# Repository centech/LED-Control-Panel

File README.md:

# LED-Control-Panel
How i created a backlit RGB-LED Control Panel for my kids (Report / DIY Guide)

- [Overview](#overview)
    + [List of used components](#list-of-used-components)
    + [Inspiration](#inspiration)
- [Report](#report)
    + [The Electronics](#the-electronics)
    + [The Panel](#the-panel)
    + [Cable Assembly](#cable-assembly)
    + [Soldering the Connector-Board](#soldering-the-connector-board)
    + [Building the wood casing](#building-the-wood-casing)
    + [Done](#done)

## Overview

Final results first of cause :)

What follows is a list of my used components, as well as a few words where i took my inspiration. Finally the detailed report with a few suggestions for potential recreations. 
But make sure to read through, since i made some glorious errors :)

### List of used components

- [LED RGB Stipes 5050 5M IP20](https://www.aliexpress.com/item/SMD-5050-3014-3528-5630-LED-Strip-RGB-Led-String-Light-Fita-de-Led-Ribbon-Bombillas/32554704554.html) (4,26 Euro per 5 meters)
- [LED Switch 3x](https://www.aliexpress.com/item/16mm-red-blue-yellow-green-white-Light-Hot-Car-Auto-Metal-LED-Power-Push-Button-Switch/32800304223.html) (1,27 Euro each)
- [LED Rocker Switch 1x](https://www.aliexpress.com/item/4pcs-lot-4models-Car-DIY-23mm-Mini-Round-Rocker-Switch-12V-16A-LED-illuminated-toggle/32801141576.html) (1,31 Euro each)
- [PWM Controler 3x](https://www.aliexpress.com/item/PWM-DC-6V-12V-24V-28V-3A-Max-Motor-Speed-Control-Module-DC-Motor-Switch-Controller/32667220339.html) (1 Euro each)
- [Cables](https://www.aliexpress.com/item/Tinned-copper-22AWG-led-RGB-cable-4-pin-RGB-cable-PVC-insulated-wire-22-awg-UL2468/32816156735.html)(0,47 Euro per meter)
- [Power Supply](https://www.amazon.de/gp/product/B01N9MSILM/ref=oh_aui_detailpage_o01_s00?ie=UTF8&psc=1) (8,99 Euro each)
- [Thread inserts 20x](https://www.ebay.de/itm/332450417100) (2,86 Euro for 20 pieces)
- [Green LED for backlighting](http://de.farnell.com/optek-technology/ovllg8c7/led-5mm-green/dp/1678694) (0.34 Euro each)
- Wood of your choice and disposal (4 Euro)

- Total material costs approx: **35 Euro**

The most expensive piece was the custom panel i made with [Ponoko](https://www.ponoko.com/) but this was mainly because of the high shipping costs to Germany.
I've used the [Black on White](https://www.ponoko.com/make-and-sell/show-material/607-acrylic-two-color-black-on-white) material. Depending on your design and shipment location you might be able to 
create this panel much cheaper.

**Panel costs:**
- Making $30.03
- Materials $12.00  
- Shiping $34.77 

Total costs approx: **96 Euro ($120)**

### Inspiration

Since i saw the [Spaceship Panel](https://imgur.com/gallery/dqK7A) Cody2084 created i wanted to make something similar for my kids. I loved the idea of creating
something - anything - which was backlit and had buttons on it :). So when i needed a bit more light in the room of my kids this was the perfect excuse to create
a **RGB-LED Control Panel**! It has to be backlit of cause (how could you see it otherwise? Its dark in the room, remeber?). And of cause it needed to have big colorful buttons.
How else would the kids be able to use it? And its not like you could simply buy these control modules, right? So in this dire situation i was practically without any other option: **i had to build it on my own**!

Before i dive into my report, i want to thank Cody2084 again for his great report on his Spaceship Panel, i hope he doesn't mind that i took quite some inspirations from it.

## Report

Ok before you start make sure that you choose the right buttons, switches and controls for your panel. The diversity is huge.

I wanted the following features/requirements fullfilled by my control panel

- LED color and brightness should be fully adjustable
- There should be a fast way to get the LED to full brightness and white color. But this feature should not wipe the settings of the custom adjusted color and brightness.
- The module shoult have an on/off switch
- All controls should have a connector, so that the panel would be easy to remove
- Of cause the module should be backlit
- I didn't want to solder the ICs on my own while i was fine with soldering a few wire lines and connectors

### The Electronics

I'm sure there are better solutions out there but i found these PWM modules to control the RGB LEDs. Its actual purpose is to control motors. But i found out that it worked just fine as a RGB controler.
So thats how it would be able to adjust each color individually. 

Now to be able to "overwrite" this settings i decided to use three switches (red, green, blue) to get each LED in full brightness mode with a simple press. 

By combining these buttons one could create a total of 7 colors (red, green, blue, cyan, magenta, yellow, white).

This is the [board schematic](/board/board.sch) i came up with. Feel free to use and optimize it. Please bear in mind that at that point i didn't think about writing a report about my project. Thats why its looking very crude.

Here is the [board layout](/board/board.brd). Red lines are cables, blue lines are soldered wires on the board. (I leave this here for completeness but do your self a favour and create your own, better schematic and layout!).

### The Panel

Beeing sure on what components to use i started designing the panel. As mentioned before I've used the [Black on White](https://www.ponoko.com/make-and-sell/show-material/607-acrylic-two-color-black-on-white) material from Ponoko. I wasn't sure if the white is translucent enough for the backlighting but since there was no other fitting material available i took the risk.
Ponoko has some easy to understand tutorials and templates. So it was easy enough to create my design. I've [uploaded it here](/panel/Panel.svg), feel free to use it as a template. 

In retrospective i would probably increase the drilling holes for the PWMs and switches to allow for a little more tolerance. Otherwise it turned out to be just perfect! Make sure to leave a big enough border, since there will be the wood frame and no backlight can reach this region. Also add a cutting line on the perimeter for a clean material cut and also include the mounting holes. By the way i used the free software [Inkscape](https://inkscape.org/) and it worked like a charm.

### Cable Assembly

As mentioned above i wanted the switches to have a connector, so the panel would be easily demountable. So its soldering time! 

Make sure you mark every signal with a specific color. And don't let your concentration slip in the process. As you might be able to tell, i got the coloring wrong on one switch and had to mark these otherwise.

The cable for the PWM needs to be open ended. Make sure to coat the ends slightly with a bit of solder.

I decided to solder the cable for the LED-Strap directly to the strap. Make sure that the cable is long enough. Do not worry if its to long, you can put the rest of it into the box later.

At last i prepared the LEDs for the backlight.

**Lessons learned**

Although i was pretty happy with the cable assembly at this time, it was not very well thought out in retrospective. In a rebuild i would certainly change the following: 

1. Make the cables **much longer**! I can't stress this enough: at least trippling the cables lenght would have saved me a lot of hassle. It seems counter intuitive at first but you can achive a much more cleard and sorted cable harness in the box if the cables are long enough. With such short cables the box seems much more crowded and its cumbersome to lift the panel and detach the connectors. Also its bad for the backlight if the cables are not sorted properly.

2. If you think you are smart by soldering connectors to your switches make at least sure that every switch gets its own connector. If not, well we will see that later.

### Soldering the Connector-Board

Since i forgot to add the power supply for the LEDs in the switches to the schematic i've added a 10 Pin Socket with 12V/GND outputs to the board afterwards.

I've also added a 12 Pin Socket (in series connected) to hook up 4 LEDs for the backlight. The suggested supply voltage for the LEDs is 3.4V. Using my 12-Pin Socket and powering it with the 12V supply i get an effective supply voltage of 3V at every LED, which works just fine. This way i didn't need to  convert the supply voltage or to use series resistors.

After thats done. Throw some voltages and ampers at it and look if it is working!

Hooray it does! I played several minutes with it, but lets get back to work.

### Panel Assembly

So now lets simply insert all the switches to the panel and thats it. Hey why do we need a chapter for this simple task anyway?

Ok here is the task: grab the below 3 switches (which are conveniently connected to 2 intertwined connectors) and click these into the 3 holes of the panel.

Sure, you would have known better than me, thats not going to work :(

So unwrap the heat shrink and disassemble the pins:

Now thread it through the holes of the panel and assemble it again.

Hooray its still working:

Feel free to skip this chapter entirely by beeing smarter than me in the first place :)

### Building the wood casing

First measure out your frame. In my case the area of the panel was 18x18cm, so i decided to make each piece of the frame 18.5x8cm. I though making the frame slightly bigger then the panel wouldn look as crude as making it smaller and it allows for some tolerances. Make sure to cut it on the right side of the line, because your blade will make the length of the pieces smaller otherwise. When measuring i add the width of the blade to the next length of the piece to compensate for that effect.

Now mark the edges of each piece. I decided to give them all a simple 45° cut and it turned out pretty good.

After the frame is done, measure out the buttom, saw it, and put everything together. If something does not fit right, you may now correct it.

In my case everything was to my satisfaction and i continue with marking all drills for the threads and cable exits.

The downside of the PWM boards is that the knob is directly soldered to the board, this way i needed the board to be on the very edge of the frame.

At that point i realized i didn't had a fitting drill for my router. So i decided to use an even more advanced tool: the **battery-powered screwdriver**!

Screwing in the threads is not so easy. I also drilled 2 holes in the backpanel to make it easiert to mount it to the wall.

Now glue the frame togher. After that glue the frame to the buttom.

In the meantime i applied a natural [oil/wax mixture](https://www.amazon.de/gp/product/B002AP6YBW/) for protection and better look.

After thats done i assembled the PWMs to the frame:

As it turns out the knobs don't stand out enough of the panel. My quick work-around was to glue a little piece of wood under the spacers. This did the trick.

To optimize the backlight i coated the inside of the box with aluminum foil.

To get an impression of the effect i made two test photos:

It may does not immediately stand out but by looking at the illumination of the flashlight, especially the silver body of it one can clearly see much improvement.

After the box was nearly finished i applied the panel to the box, marked the holes for the mouting and put it the threads.

Since everything worked out, i finally glued it the power supply socket and mounted the 4 backlight LEDs to the frame:

### Done

Finally done! I'm very pleased how it turned out. The backlight effect is better than i hoped for. As always there are quite a few things i would have done different in retrospective, above all allowing for much longer cables to be able to mount the cables to the frame. This wasn't possible this time and effects the handling and backlight. But all in all it was a very fun project and i am very happy how it turned out.

Mounting it to the wall and let the kids play.
Ofcause I need to regularly test it to insure its still working properly :)

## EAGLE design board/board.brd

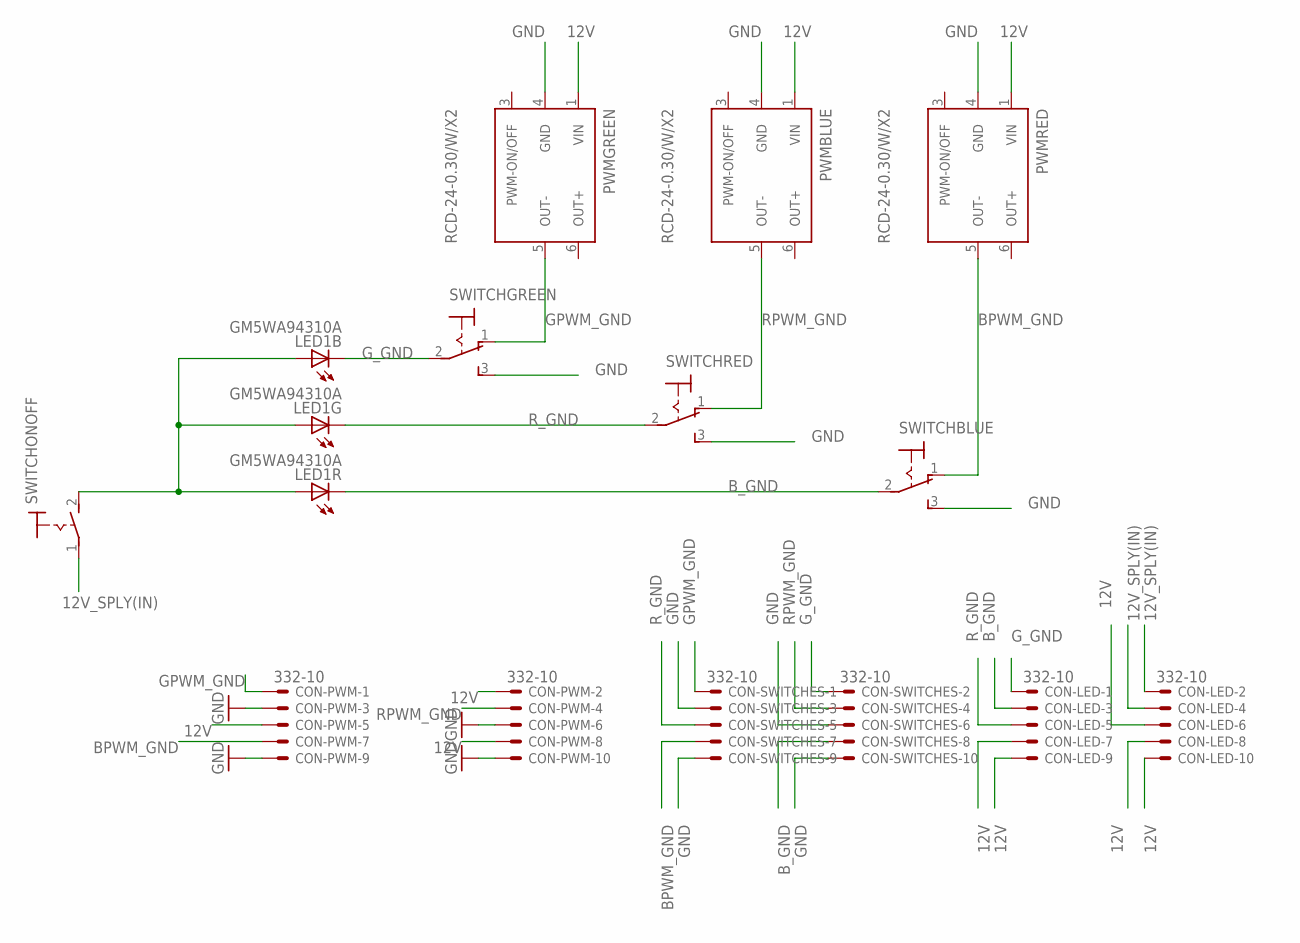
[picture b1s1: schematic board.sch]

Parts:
CON-LED: 332-10
CON-PWM: 332-10
CON-SWITCHES: 332-10
LED1: GM5WA94310A
PWMBLUE: RCD-24-0.30/W/X2; RCD-24/W/X2
PWMGREEN: RCD-24-0.30/W/X2; RCD-24/W/X2
PWMRED: RCD-24-0.30/W/X2; RCD-24/W/X2
SWITCHBLUE: M9040P
SWITCHGREEN: M9040P
SWITCHONOFF: MS243
SWITCHRED: M9040P

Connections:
12V: CON-LED.6, CON-LED.7, CON-LED.8, CON-LED.9, CON-LED.10, CON-PWM.2, CON-PWM.5, CON-PWM.8, LED1.1 (A), LED1.2 (A), LED1.3 (A), PWMBLUE.1 (VIN), PWMGREEN.1 (VIN), PWMRED.1 (VIN), SWITCHONOFF.2 (S)
12V_SPLY(IN): CON-LED.2, CON-LED.4, SWITCHONOFF.1
BPWM_GND: CON-PWM.7, CON-SWITCHES.7, PWMRED.5 (OUT-), SWITCHBLUE.1 (O)
B_GND: CON-LED.3, CON-SWITCHES.8, LED1.5 (C), SWITCHBLUE.2
GND: CON-PWM.3, CON-PWM.6, CON-PWM.9, CON-PWM.10, CON-SWITCHES.3, CON-SWITCHES.6, CON-SWITCHES.9, CON-SWITCHES.10, PWMBLUE.4 (GND), PWMGREEN.4 (GND), PWMRED.4 (GND), SWITCHBLUE.3 (S), SWITCHGREEN.3 (S), SWITCHRED.3 (S)
GPWM_GND: CON-PWM.1, CON-SWITCHES.1, PWMGREEN.5 (OUT-), SWITCHGREEN.1 (O)
G_GND: CON-LED.1, CON-SWITCHES.2, LED1.6 (C), SWITCHGREEN.2
RPWM_GND: CON-PWM.4, CON-SWITCHES.4, PWMBLUE.5 (OUT-), SWITCHRED.1 (O)
R_GND: CON-LED.5, CON-SWITCHES.5, LED1.4 (C), SWITCHRED.2

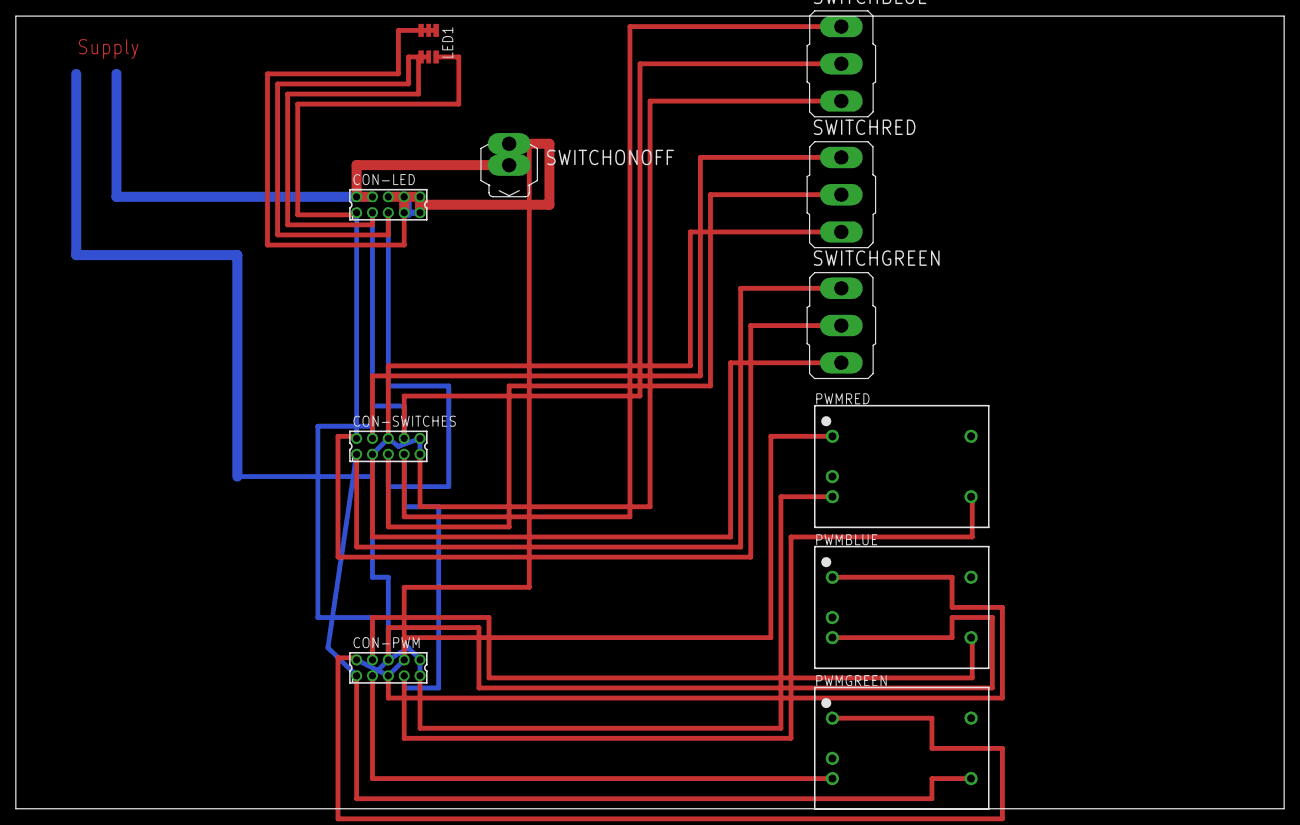
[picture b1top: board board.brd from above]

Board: 2 copper layers, 160.0 x 100.0 mm, 11 parts (0 on the bottom side), 9 nets.

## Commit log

2018-03-26 init
2018-03-27 added images
2018-03-27 added panel and board files
2018-03-28 adding pictures
2018-03-28 added fotos
2018-03-28 adding
2018-03-28 adding more fotos
2018-03-28 foto
